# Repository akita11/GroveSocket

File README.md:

# GroveSocket

Groveコネクタを4ピンの着脱可能なネジ端子に変換します。またGrove端子の4本を観測などのために引き出す端子（ピンソケット等を接続可能）も備えています。またM5StackのUNITと同一の基板形状のため、ケースを流用できます。

## Author

Junichi Akita (akita@ifdl.jp, @akita11)

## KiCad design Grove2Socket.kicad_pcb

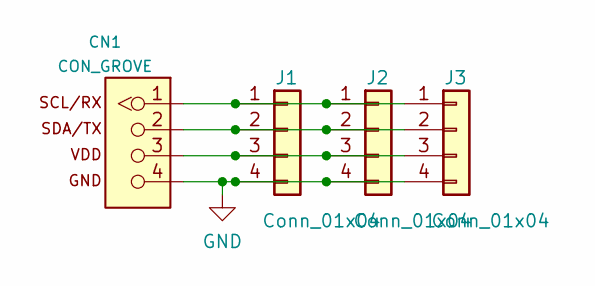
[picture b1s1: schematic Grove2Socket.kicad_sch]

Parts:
CN1: CON_GROVE; CON_GROVE_H
J1, J3: Conn_01x04; PinSocket_1x04_P2.54mm_Vertical
J2: Conn_01x04; CON_HT396R_4P

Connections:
GND: CN1.4, J1.4, J2.4, J3.4
unnamed: CN1.1, J1.1, J2.1, J3.1
unnamed: CN1.2, J1.2, J2.2, J3.2
unnamed: CN1.3, J1.3, J2.3, J3.3

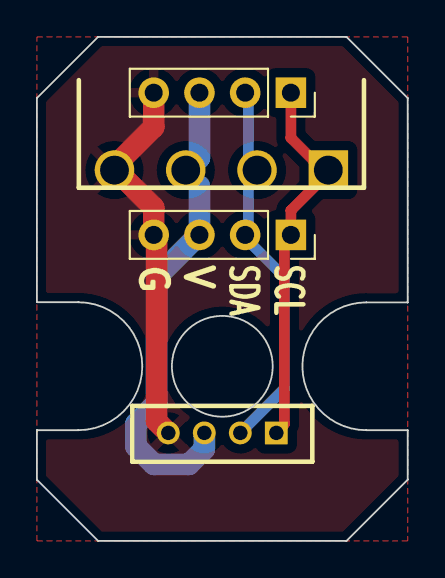
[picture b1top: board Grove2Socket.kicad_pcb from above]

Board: 2 copper layers, 20.6 x 28.0 mm, 4 parts (0 on the bottom side), 4 nets.
